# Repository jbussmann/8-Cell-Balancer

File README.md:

# 8-Cell Balancer Charger
This is the repository of a prototype 8-Cell Balancer Charger I have been working on for quite some time. If you would like to follow the development progress, feel free to visit my streams at https://www.twitch.tv/jbussmann where I usually work on this project.

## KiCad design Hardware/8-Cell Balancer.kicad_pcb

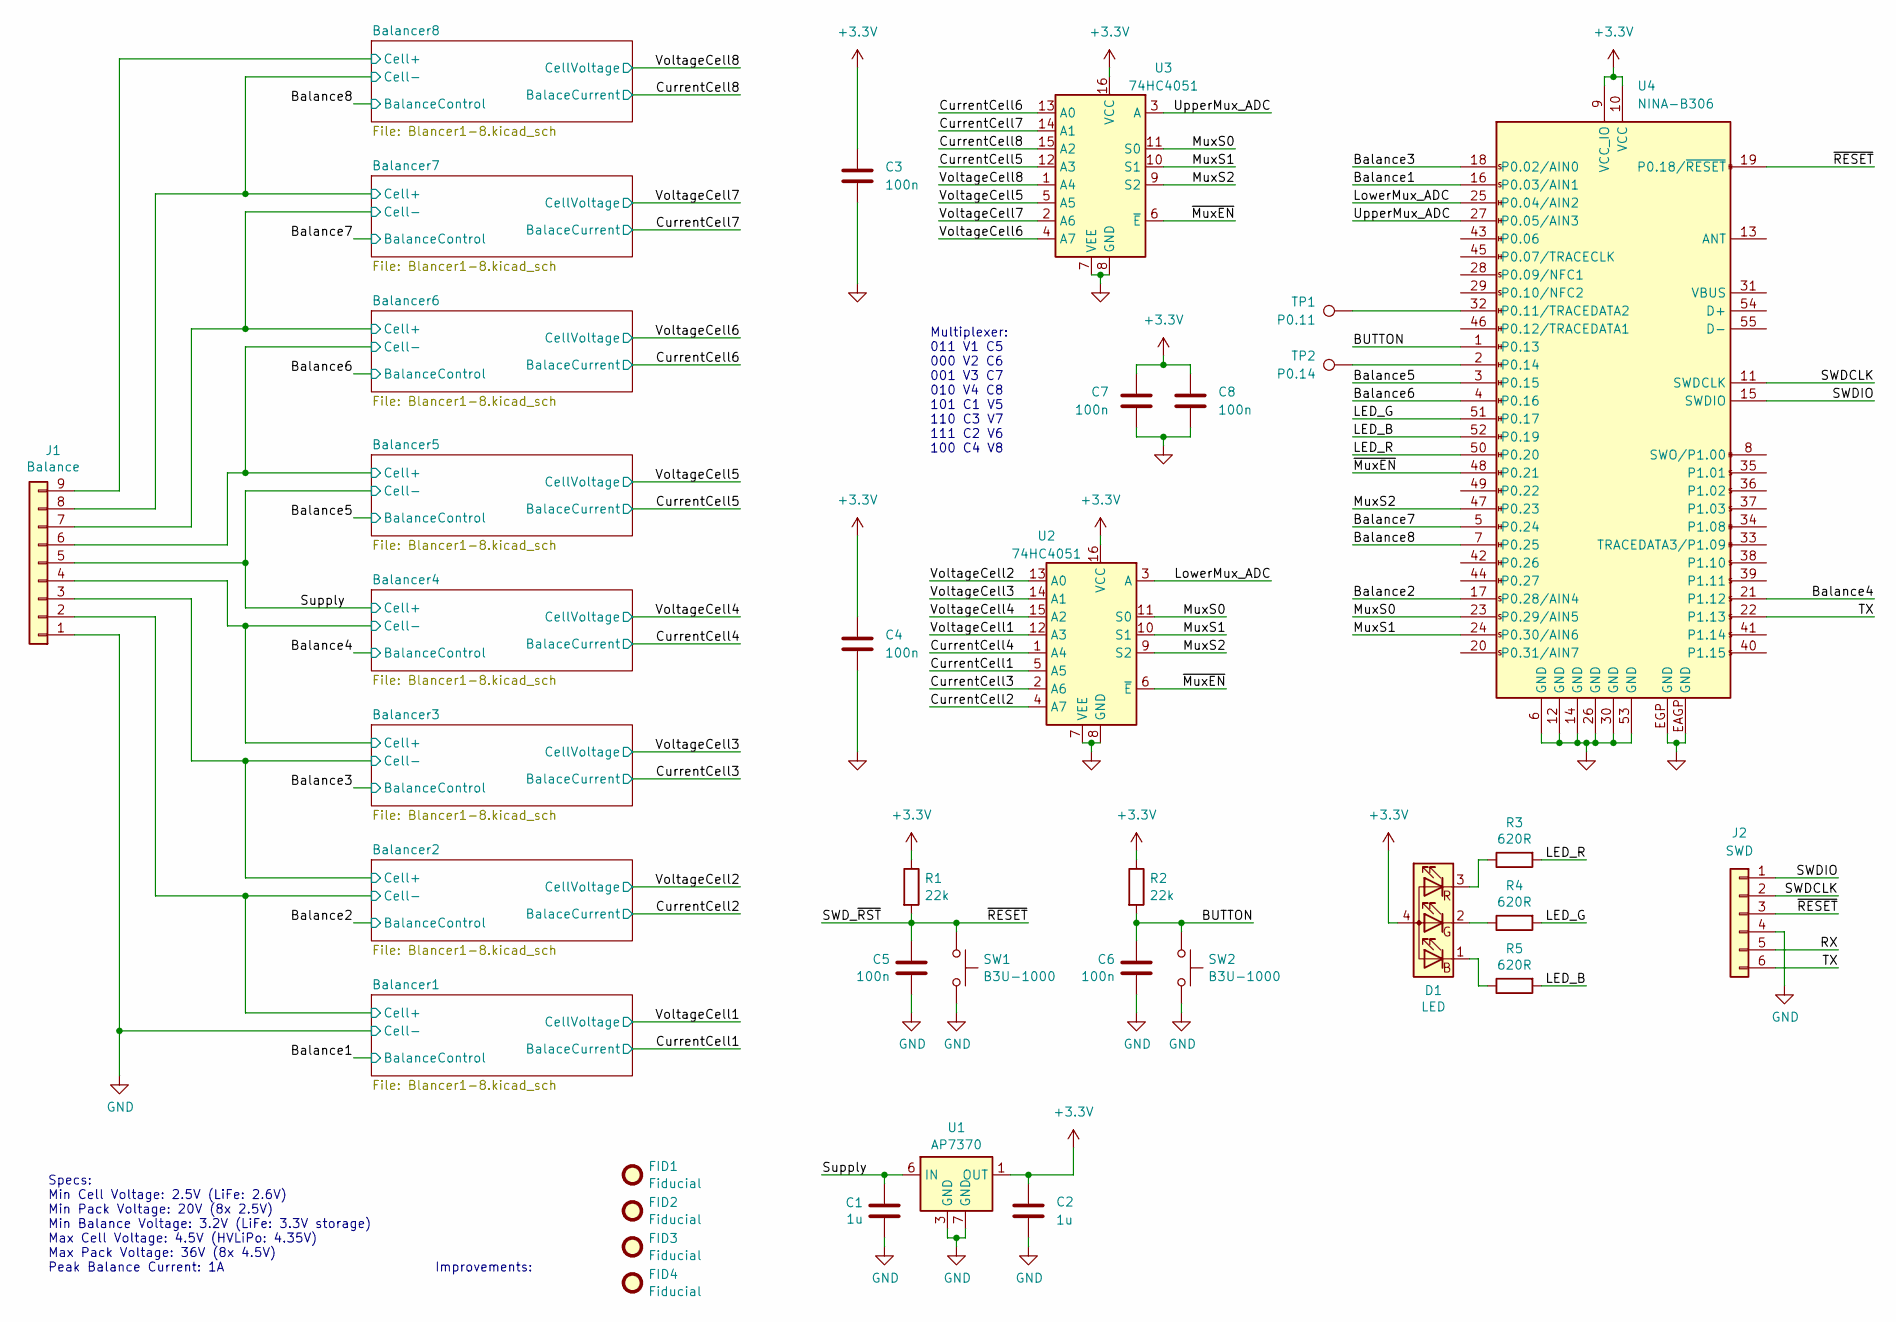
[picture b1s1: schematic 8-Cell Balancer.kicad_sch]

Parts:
C1, C2: 1u; C_0603_1608Metric; Mfr. Part# GRT188R61H105KE13D; Mouser Part# 81-GRT188R61H105KE3D
C3, C4, C5, C6, C7, C8: 100n; C_0402_1005Metric; Mfr. Part# GRM155R71C104KA88D; Mouser Part# 81-GRM155R71C104KA88
D1: LED; LED_RGB_1x1mm; Mfr. Part# UHD1110-FKA-CL1A13r3q1BBQFMF3; Mouser Part# 941-UHD0FKAC11BQFMF3
FID1, FID2, FID3, FID4: Fiducial; Fiducial_1mm_Mask2mm
J1: Balance; PinHeader_1x09_P2.54mm_Vertical
J2: SWD; PinHeader_1x06_P1.27mm_Vertical
R1, R2: 22k; R_0402_1005Metric; Mfr. Part# RC0402FR-0722KL; Mouser Part# 603-RC0402FR-0722KL
R3, R4, R5: 620R; R_0402_1005Metric; Mfr. Part# RC0402FR-07620RL; Mouser Part# 603-RC0402FR-07620RL
SW1, SW2: B3U-1000; Button_B3U-1000; Mfr. Part# B3U-1000P-B; Mouser Part# 653-B3U-1000P-B
TP1: P0.11; TestPoint_Pad_D1.0mm
TP2: P0.14; TestPoint_Pad_D1.0mm
U1: AP7370; Diodes_UDFN2020-6; Mfr. Part# AP7370-33FDC-7; Mouser Part# 621-AP7370-33FDC-7
U2, U3: 74HC4051; QFN-16-1EP_2.5x3.5mm_P0.5mm_EP1x2.5mm; Mfr. Part# 74LV4051BQ,115; Mouser Part# 771-LV4051BQ115
U4: NINA-B306; Module_ublox_NINA-B306; Mfr. Part# NINA-B306-00B; Mouser Part# 377-NINA-B306-00B

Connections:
+3.3V: C2.1, C3.1, C4.1, C7.1, C8.1, D1.4 (A), R1.1, R2.1, U1.1 (OUT), U2.16 (VCC), U3.16 (VCC), U4.9 (VCC_IO), U4.10 (VCC)
/BUTTON: C6.1, R2.2, SW2.1, U4.1 (P0.13)
/Balance1: U4.16 (P0.03/AIN1); also elsewhere on the board
/Balance2: U4.17 (P0.28/AIN4); also elsewhere on the board
/Balance3: U4.18 (P0.02/AIN0); also elsewhere on the board
/Balance4: U4.21 (P1.12); also elsewhere on the board
/Balance5: U4.3 (P0.15); also elsewhere on the board
/Balance6: U4.4 (P0.16); also elsewhere on the board
/Balance7: U4.5 (P0.24); also elsewhere on the board
/Balance8: U4.7 (P0.25); also elsewhere on the board
/Balancer1/Cell+: J1.2; also elsewhere on the board
/Balancer2/Cell+: J1.3; also elsewhere on the board
/Balancer3/Cell+: J1.4; also elsewhere on the board
/Balancer5/Cell+: J1.6; also elsewhere on the board
/Balancer6/Cell+: J1.7; also elsewhere on the board
/Balancer7/Cell+: J1.8; also elsewhere on the board
/Balancer8/Cell+: J1.9; also elsewhere on the board
/CurrentCell1: U2.5 (A5); also elsewhere on the board
/CurrentCell2: U2.4 (A7); also elsewhere on the board
/CurrentCell3: U2.2 (A6); also elsewhere on the board
/CurrentCell4: U2.1 (A4); also elsewhere on the board
/CurrentCell5: U3.12 (A3); also elsewhere on the board
/CurrentCell6: U3.13 (A0); also elsewhere on the board
/CurrentCell7: U3.14 (A1); also elsewhere on the board
/CurrentCell8: U3.15 (A2); also elsewhere on the board
/LED_B: R5.2, U4.52 (P0.19)
/LED_G: R4.2, U4.51 (P0.17)
/LED_R: R3.2, U4.50 (P0.20)
/LowerMux_ADC: U2.3 (A), U4.25 (P0.04/AIN2)
/MuxS0: U2.11 (S0), U3.11 (S0), U4.23 (P0.29/AIN5)
/MuxS1: U2.10 (S1), U3.10 (S1), U4.24 (P0.30/AIN6)
/MuxS2: U2.9 (S2), U3.9 (S2), U4.47 (P0.23)
/RX: J2.5
/SWDCLK: J2.2, U4.11 (SWDCLK)
/SWDIO: J2.1, U4.15 (SWDIO)
/SWD_~RST: C5.1, J2.3, R1.2, SW1.1, U4.19 (P0.18/~RESET)
/Supply: C1.1, J1.5, U1.6 (IN); also elsewhere on the board
/TX: J2.6, U4.22 (P1.13)
/UpperMux_ADC: U3.3 (A), U4.27 (P0.05/AIN3)
/VoltageCell1: U2.12 (A3); also elsewhere on the board
/VoltageCell2: U2.13 (A0); also elsewhere on the board
/VoltageCell3: U2.14 (A1); also elsewhere on the board
/VoltageCell4: U2.15 (A2); also elsewhere on the board
/VoltageCell5: U3.5 (A5); also elsewhere on the board
/VoltageCell6: U3.4 (A7); also elsewhere on the board
/VoltageCell7: U3.2 (A6); also elsewhere on the board
/VoltageCell8: U3.1 (A4); also elsewhere on the board
/~MuxEN: U2.6 (~E), U3.6 (~E), U4.48 (P0.21)
GND: C1.2, C2.2, C3.2, C4.2, C5.2, C6.2, C7.2, C8.2, J1.1, J2.4, SW1.2, SW2.2, U1.3 (GND), U1.7 (GND), U2.7 (VEE), U2.8 (GND), U3.7 (VEE), U3.8 (GND), U4.6 (GND), U4.12 (GND), U4.14 (GND), U4.26 (GND), U4.30 (GND), U4.53 (GND), U4.EAGP (GND), U4.EGP (GND); also elsewhere on the board
unnamed: D1.1 (BK), R5.1
unnamed: D1.2 (GK), R4.1
unnamed: D1.3 (RK), R3.1
unnamed: TP1.1, U4.32 (P0.11/TRACEDATA2)
unnamed: TP2.1, U4.2 (P0.14)

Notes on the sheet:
Improvements:
Specs: Min Cell Voltage: 2.5V (LiFe: 2.6V) Min Pack Voltage: 20V (8x 2.5V) Min Balance Voltage: 3.2V (LiFe: 3.3V storage) Max Cell Voltage: 4.5V (HVLiPo: 4.35V) Max Pack Voltage: 36V (8x 4.5V) Peak Balance Current: 1A
Multiplexer: 011 V1 C5 000 V2 C6 001 V3 C7 010 V4 C8 101 C1 V5 110 C3 V7 111 C2 V6 100 C4 V8

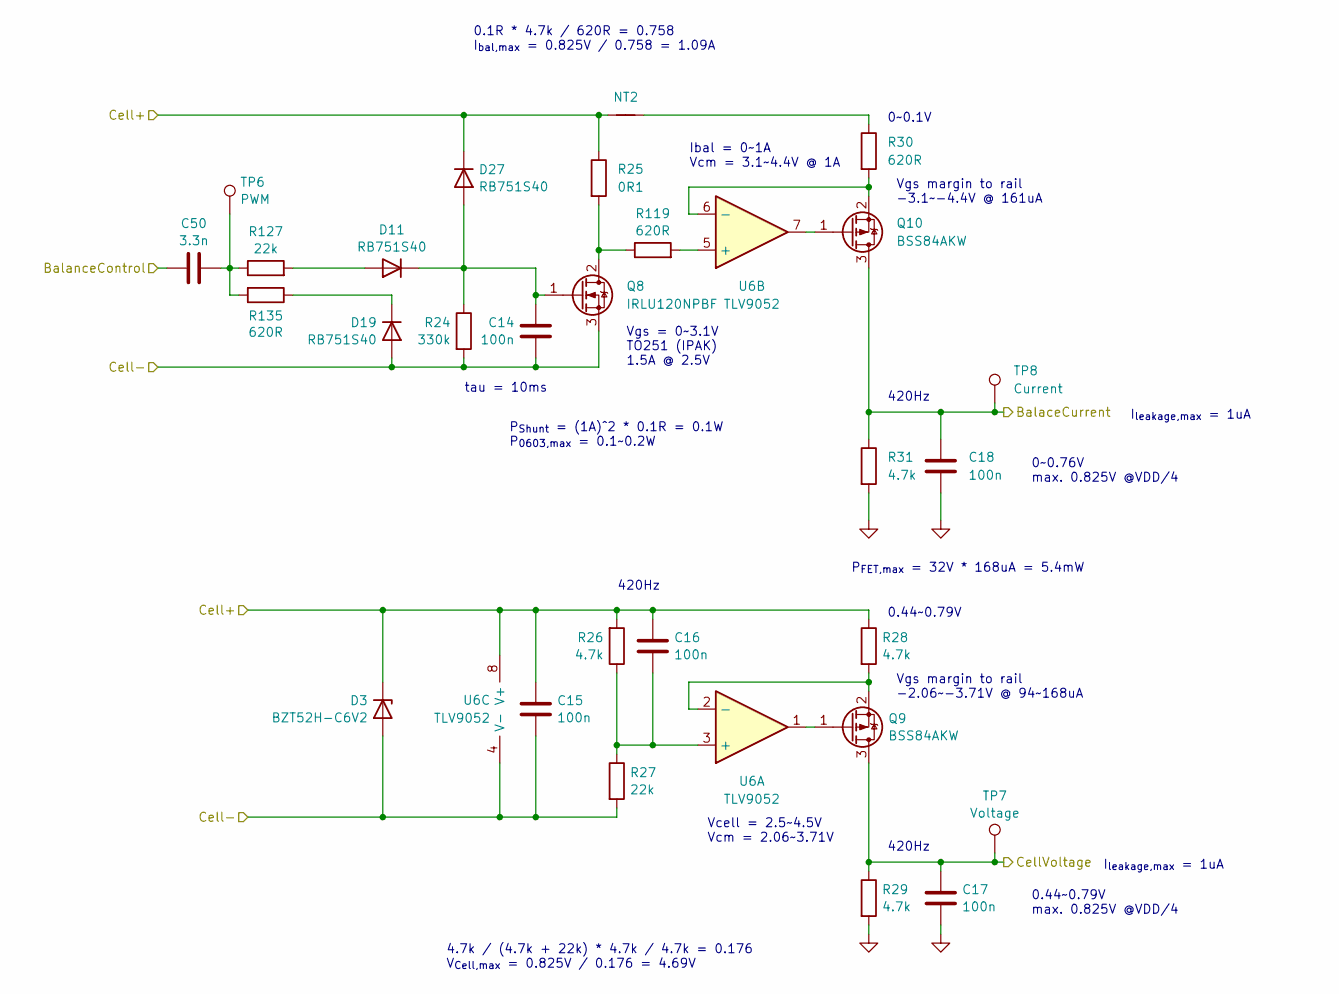
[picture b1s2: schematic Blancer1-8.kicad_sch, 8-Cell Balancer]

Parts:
C14, C15, C16, C17, C18: 100n; C_0402_1005Metric; Mfr. Part# GRM155R71C104KA88D; Mouser Part# 81-GRM155R71C104KA88
C50: 3.3n; C_0402_1005Metric; Mfr. Part# GRM1555C1H332JE01D; Mouser Part# 81-GRM1555C1H332JE1D
D3: BZT52H-C6V2; D_SOD-123F; Mfr. Part# BZT52H-C6V2,115; Mouser Part# 771-BZT52H-C6V2-T/R
D11, D19, D27: RB751S40; D_SOD-523; Mfr. Part# RB751S40T5G; Mouser Part# 863-RB751S40T5G
NT2: NetTie; NetTie-2_SMD_Pad0.127mm
Q8: IRLU120NPBF; TO-251-3_Flipped; Mfr. Part# IRLU120NPBF; Mouser Part# 942-IRLU120NPBF
Q9, Q10: BSS84AKW; SOT-323_SC-70; Mfr. Part# BSS84AKW,115; Mouser Part# 771-BSS84AKW115
R24: 330k; R_0402_1005Metric; Mfr. Part# RC0402FR-0722KL; Mouser Part# 603-RC0402FR-0722KL
R25: 0R1; R_0603_1608Metric; Mfr. Part# PT0603FR-7W0R1L; Mouser Part# 603-PT0603FR-7W0R1L
R26, R28, R29, R31: 4.7k; R_0402_1005Metric; Mfr. Part# RC0402FR-134K7L; Mouser Part# 603-RC0402FR-134K7L
R27, R127: 22k; R_0402_1005Metric; Mfr. Part# RC0402FR-0722KL; Mouser Part# 603-RC0402FR-0722KL
R30, R119, R135: 620R; R_0402_1005Metric; Mfr. Part# RC0402FR-07620RL; Mouser Part# 603-RC0402FR-07620RL
TP6: PWM; TestPoint_Pad_D1.0mm
TP7: Voltage; TestPoint_Pad_D1.0mm
TP8: Current; TestPoint_Pad_D1.0mm
U6: TLV9052; SOT-23-8; Mfr. Part# TLV9052IDDFR; Mouser Part# 595-TLV9052IDDFR

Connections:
/Balance2: C50.1; also elsewhere on the board
/Balancer1/Cell+: C14.2, C15.2, D3.2 (A), D19.2 (A), Q8.3 (S), R24.2, R27.2, U6.4 (V-); also elsewhere on the board
/Balancer2/Cell+: C15.1, C16.1, D3.1 (K), D27.1 (K), NT2.1, R25.1, R26.2, R28.1, U6.8 (V+); also elsewhere on the board
/CurrentCell2: C18.1, Q10.3 (D), R31.1, TP8.1; also elsewhere on the board
/VoltageCell2: C17.1, Q9.3 (D), R29.1, TP7.1; also elsewhere on the board
GND: C17.2, C18.2, R29.2, R31.2; also elsewhere on the board
unnamed: C50.2, R127.1, R135.2, TP6.1
unnamed: D11.2 (A), R127.2
unnamed: C14.1, D11.1 (K), D27.2 (A), Q8.1 (G), R24.1
unnamed: D19.1 (K), R135.1
unnamed: NT2.2, R30.1
unnamed: Q8.2 (D), R25.2, R119.1
unnamed: Q9.1 (G), U6.1
unnamed: Q9.2 (S), R28.2, U6.2 (-)
unnamed: Q10.1 (G), U6.7
unnamed: Q10.2 (S), R30.2, U6.6 (-)
unnamed: C16.2, R26.1, R27.1, U6.3 (+)
unnamed: R119.2, U6.5 (+)

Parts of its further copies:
C9, C10, C11, C12, C13, C19, C20, C21, C22, C23, C24, C25, C26, C27, C28, C29, C30, C31, C32, C33, C34, C35, C36, C37, C38, C39, C40, C41, C42, C43, C44, C45, C46, C47, C48: 100n; C_0402_1005Metric; Mfr. Part# GRM155R71C104KA88D; Mouser Part# 81-GRM155R71C104KA88
C49, C51, C52, C53, C54, C55, C56: 3.3n; C_0402_1005Metric; Mfr. Part# GRM1555C1H332JE01D; Mouser Part# 81-GRM1555C1H332JE1D
D2, D4, D5, D6, D7, D8, D9: BZT52H-C6V2; D_SOD-123F; Mfr. Part# BZT52H-C6V2,115; Mouser Part# 771-BZT52H-C6V2-T/R
D10, D12, D13, D14, D15, D16, D17, D18, D20, D21, D22, D23, D24, D25, D26, D28, D29, D30, D31, D32, D33: RB751S40; D_SOD-523; Mfr. Part# RB751S40T5G; Mouser Part# 863-RB751S40T5G
NT1, NT3, NT4, NT5, NT6, NT7, NT8: NetTie; NetTie-2_SMD_Pad0.127mm
Q3, Q13, Q18, Q23, Q28, Q33, Q38: IRLU120NPBF; TO-251-3_Flipped; Mfr. Part# IRLU120NPBF; Mouser Part# 942-IRLU120NPBF
Q4, Q5, Q14, Q15, Q19, Q20, Q24, Q25, Q29, Q30, Q34, Q35, Q39, Q40: BSS84AKW; SOT-323_SC-70; Mfr. Part# BSS84AKW,115; Mouser Part# 771-BSS84AKW115
R11, R37, R50, R63, R76, R89, R102: 330k; R_0402_1005Metric; Mfr. Part# RC0402FR-0722KL; Mouser Part# 603-RC0402FR-0722KL
R12, R38, R51, R64, R77, R90, R103: 0R1; R_0603_1608Metric; Mfr. Part# PT0603FR-7W0R1L; Mouser Part# 603-PT0603FR-7W0R1L
R13, R15, R16, R18, R39, R41, R42, R44, R52, R54, R55, R57, R65, R67, R68, R70, R78, R80, R81, R83, R91, R93, R94, R96, R104, R106, R107, R109: 4.7k; R_0402_1005Metric; Mfr. Part# RC0402FR-134K7L; Mouser Part# 603-RC0402FR-134K7L
R14, R40, R53, R66, R79, R92, R105, R126, R128, R129, R130, R131, R132, R133: 22k; R_0402_1005Metric; Mfr. Part# RC0402FR-0722KL; Mouser Part# 603-RC0402FR-0722KL
R17, R43, R56, R69, R82, R95, R108, R118, R120, R121, R122, R123, R124, R125, R134, R136, R137, R138, R139, R140, R141: 620R; R_0402_1005Metric; Mfr. Part# RC0402FR-07620RL; Mouser Part# 603-RC0402FR-07620RL
TP3, TP9, TP12, TP15, TP18, TP21, TP24: PWM; TestPoint_Pad_D1.0mm
TP4, TP10, TP13, TP16, TP19, TP22, TP25: Voltage; TestPoint_Pad_D1.0mm
TP5, TP11, TP14, TP17, TP20, TP23, TP26: Current; TestPoint_Pad_D1.0mm
U5, U7, U8, U9, U10, U11, U12: TLV9052; SOT-23-8; Mfr. Part# TLV9052IDDFR; Mouser Part# 595-TLV9052IDDFR

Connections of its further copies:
/Balance1: C49.1; also elsewhere on the board
/Balance3: C51.1; also elsewhere on the board
/Balance4: C52.1; also elsewhere on the board
/Balance5: C53.1; also elsewhere on the board
/Balance6: C54.1; also elsewhere on the board
/Balance7: C55.1; also elsewhere on the board
/Balance8: C56.1; also elsewhere on the board
/Balancer1/Cell+: C10.1, C11.1, D2.1 (K), D26.1 (K), NT1.1, R12.1, R13.2, R15.1, U5.8 (V+); also elsewhere on the board
/Balancer2/Cell+: C19.2, C20.2, D4.2 (A), D20.2 (A), Q13.3 (S), R37.2, R40.2, U7.4 (V-); also elsewhere on the board
/Balancer3/Cell+: C20.1, C21.1, C24.2, C25.2, D4.1 (K), D5.2 (A), D21.2 (A), D28.1 (K), NT3.1, Q18.3 (S), R38.1, R39.2, R41.1, R50.2, R53.2, U7.8 (V+), U8.4 (V-); also elsewhere on the board
/Balancer5/Cell+: C30.1, C31.1, C34.2, C35.2, D6.1 (K), D7.2 (A), D23.2 (A), D30.1 (K), NT5.1, Q28.3 (S), R64.1, R65.2, R67.1, R76.2, R79.2, U9.8 (V+), U10.4 (V-); also elsewhere on the board
/Balancer6/Cell+: C35.1, C36.1, C39.2, C40.2, D7.1 (K), D8.2 (A), D24.2 (A), D31.1 (K), NT6.1, Q33.3 (S), R77.1, R78.2, R80.1, R89.2, R92.2, U10.8 (V+), U11.4 (V-); also elsewhere on the board
/Balancer7/Cell+: C40.1, C41.1, C44.2, C45.2, D8.1 (K), D9.2 (A), D25.2 (A), D32.1 (K), NT7.1, Q38.3 (S), R90.1, R91.2, R93.1, R102.2, R105.2, U11.8 (V+), U12.4 (V-); also elsewhere on the board
/Balancer8/Cell+: C45.1, C46.1, D9.1 (K), D33.1 (K), NT8.1, R103.1, R104.2, R106.1, U12.8 (V+); also elsewhere on the board
/CurrentCell1: C13.1, Q5.3 (D), R18.1, TP5.1; also elsewhere on the board
/CurrentCell3: C23.1, Q15.3 (D), R44.1, TP11.1; also elsewhere on the board
/CurrentCell4: C28.1, Q20.3 (D), R57.1, TP14.1; also elsewhere on the board
/CurrentCell5: C33.1, Q25.3 (D), R70.1, TP17.1; also elsewhere on the board
/CurrentCell6: C38.1, Q30.3 (D), R83.1, TP20.1; also elsewhere on the board
/CurrentCell7: C43.1, Q35.3 (D), R96.1, TP23.1; also elsewhere on the board
/CurrentCell8: C48.1, Q40.3 (D), R109.1, TP26.1; also elsewhere on the board
/Supply: C25.1, C26.1, C29.2, C30.2, D5.1 (K), D6.2 (A), D22.2 (A), D29.1 (K), NT4.1, Q23.3 (S), R51.1, R52.2, R54.1, R63.2, R66.2, U8.8 (V+), U9.4 (V-); also elsewhere on the board
/VoltageCell1: C12.1, Q4.3 (D), R16.1, TP4.1; also elsewhere on the board
/VoltageCell3: C22.1, Q14.3 (D), R42.1, TP10.1; also elsewhere on the board
/VoltageCell4: C27.1, Q19.3 (D), R55.1, TP13.1; also elsewhere on the board
/VoltageCell5: C32.1, Q24.3 (D), R68.1, TP16.1; also elsewhere on the board
/VoltageCell6: C37.1, Q29.3 (D), R81.1, TP19.1; also elsewhere on the board
/VoltageCell7: C42.1, Q34.3 (D), R94.1, TP22.1; also elsewhere on the board
/VoltageCell8: C47.1, Q39.3 (D), R107.1, TP25.1; also elsewhere on the board
GND: C9.2, C10.2, C12.2, C13.2, C22.2, C23.2, C27.2, C28.2, C32.2, C33.2, C37.2, C38.2, C42.2, C43.2, C47.2, C48.2, D2.2 (A), D18.2 (A), Q3.3 (S), R11.2, R14.2, R16.2, R18.2, R42.2, R44.2, R55.2, R57.2, R68.2, R70.2, R81.2, R83.2, R94.2, R96.2, R107.2, R109.2, U5.4 (V-); also elsewhere on the board
unnamed: C49.2, R126.1, R134.2, TP3.1
unnamed: C51.2, R128.1, R136.2, TP9.1
unnamed: C52.2, R129.1, R137.2, TP12.1
unnamed: C53.2, R130.1, R138.2, TP15.1
unnamed: C54.2, R131.1, R139.2, TP18.1
unnamed: C55.2, R132.1, R140.2, TP21.1
unnamed: C56.2, R133.1, R141.2, TP24.1
unnamed: D10.2 (A), R126.2
unnamed: C9.1, D10.1 (K), D26.2 (A), Q3.1 (G), R11.1
unnamed: D12.2 (A), R128.2
unnamed: C19.1, D12.1 (K), D28.2 (A), Q13.1 (G), R37.1
unnamed: D13.2 (A), R129.2
unnamed: C24.1, D13.1 (K), D29.2 (A), Q18.1 (G), R50.1
unnamed: D14.2 (A), R130.2
unnamed: C29.1, D14.1 (K), D30.2 (A), Q23.1 (G), R63.1
unnamed: D15.2 (A), R131.2
unnamed: C34.1, D15.1 (K), D31.2 (A), Q28.1 (G), R76.1
unnamed: D16.2 (A), R132.2
unnamed: C39.1, D16.1 (K), D32.2 (A), Q33.1 (G), R89.1
unnamed: D17.2 (A), R133.2
unnamed: C44.1, D17.1 (K), D33.2 (A), Q38.1 (G), R102.1
unnamed: D18.1 (K), R134.1
unnamed: D20.1 (K), R136.1
unnamed: D21.1 (K), R137.1
unnamed: D22.1 (K), R138.1
unnamed: D23.1 (K), R139.1
unnamed: D24.1 (K), R140.1
unnamed: D25.1 (K), R141.1
unnamed: NT1.2, R17.1
unnamed: NT3.2, R43.1
unnamed: NT4.2, R56.1
unnamed: NT5.2, R69.1
unnamed: NT6.2, R82.1
unnamed: NT7.2, R95.1
unnamed: NT8.2, R108.1
unnamed: Q3.2 (D), R12.2, R118.1
unnamed: Q4.1 (G), U5.1
unnamed: Q4.2 (S), R15.2, U5.2 (-)
unnamed: Q5.1 (G), U5.7
unnamed: Q5.2 (S), R17.2, U5.6 (-)
unnamed: Q13.2 (D), R38.2, R120.1
unnamed: Q14.1 (G), U7.1
unnamed: Q14.2 (S), R41.2, U7.2 (-)
unnamed: Q15.1 (G), U7.7
unnamed: Q15.2 (S), R43.2, U7.6 (-)
unnamed: Q18.2 (D), R51.2, R121.1
unnamed: Q19.1 (G), U8.1
unnamed: Q19.2 (S), R54.2, U8.2 (-)
unnamed: Q20.1 (G), U8.7
unnamed: Q20.2 (S), R56.2, U8.6 (-)
unnamed: Q23.2 (D), R64.2, R122.1
unnamed: Q24.1 (G), U9.1
unnamed: Q24.2 (S), R67.2, U9.2 (-)
unnamed: Q25.1 (G), U9.7
unnamed: Q25.2 (S), R69.2, U9.6 (-)
unnamed: Q28.2 (D), R77.2, R123.1
unnamed: Q29.1 (G), U10.1
unnamed: Q29.2 (S), R80.2, U10.2 (-)
unnamed: Q30.1 (G), U10.7
unnamed: Q30.2 (S), R82.2, U10.6 (-)
unnamed: Q33.2 (D), R90.2, R124.1
unnamed: Q34.1 (G), U11.1
unnamed: Q34.2 (S), R93.2, U11.2 (-)
unnamed: Q35.1 (G), U11.7
unnamed: Q35.2 (S), R95.2, U11.6 (-)
unnamed: Q38.2 (D), R103.2, R125.1
unnamed: Q39.1 (G), U12.1
unnamed: Q39.2 (S), R106.2, U12.2 (-)
unnamed: Q40.1 (G), U12.7
unnamed: Q40.2 (S), R108.2, U12.6 (-)
unnamed: C11.2, R13.1, R14.1, U5.3 (+)
unnamed: R118.2, U5.5 (+)
unnamed: C21.2, R39.1, R40.1, U7.3 (+)
unnamed: R120.2, U7.5 (+)
unnamed: C26.2, R52.1, R53.1, U8.3 (+)
unnamed: R121.2, U8.5 (+)
unnamed: C31.2, R65.1, R66.1, U9.3 (+)
unnamed: R122.2, U9.5 (+)
unnamed: C36.2, R78.1, R79.1, U10.3 (+)
unnamed: R123.2, U10.5 (+)
unnamed: C41.2, R91.1, R92.1, U11.3 (+)
unnamed: R124.2, U11.5 (+)
unnamed: C46.2, R104.1, R105.1, U12.3 (+)
unnamed: R125.2, U12.5 (+)

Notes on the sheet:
P_{FET,max} = 32V * 168uA = 5.4mW
420Hz
tau = 10ms
Vgs margin to rail -3.1~-4.4V @ 161uA
I_{leakage,max} = 1uA
P_{Shunt} = (1A)^2 * 0.1R = 0.1W P_{0603,max} = 0.1~0.2W
0.44~0.79V max. 0.825V @VDD/4
Vgs margin to rail -2.06~-3.71V @ 94~168uA
Vgs = 0~3.1V TO251 (IPAK) 1.5A @ 2.5V
Ibal = 0~1A Vcm = 3.1~4.4V @ 1A
4.7k / (4.7k + 22k) * 4.7k / 4.7k = 0.176 V_{Cell,max} = 0.825V / 0.176 = 4.69V
0.44~0.79V
0.1R * 4.7k / 620R = 0.758 I_{bal,max} = 0.825V / 0.758 = 1.09A
0~0.76V max. 0.825V @VDD/4
0~0.1V
Vcell = 2.5~4.5V Vcm = 2.06~3.71V

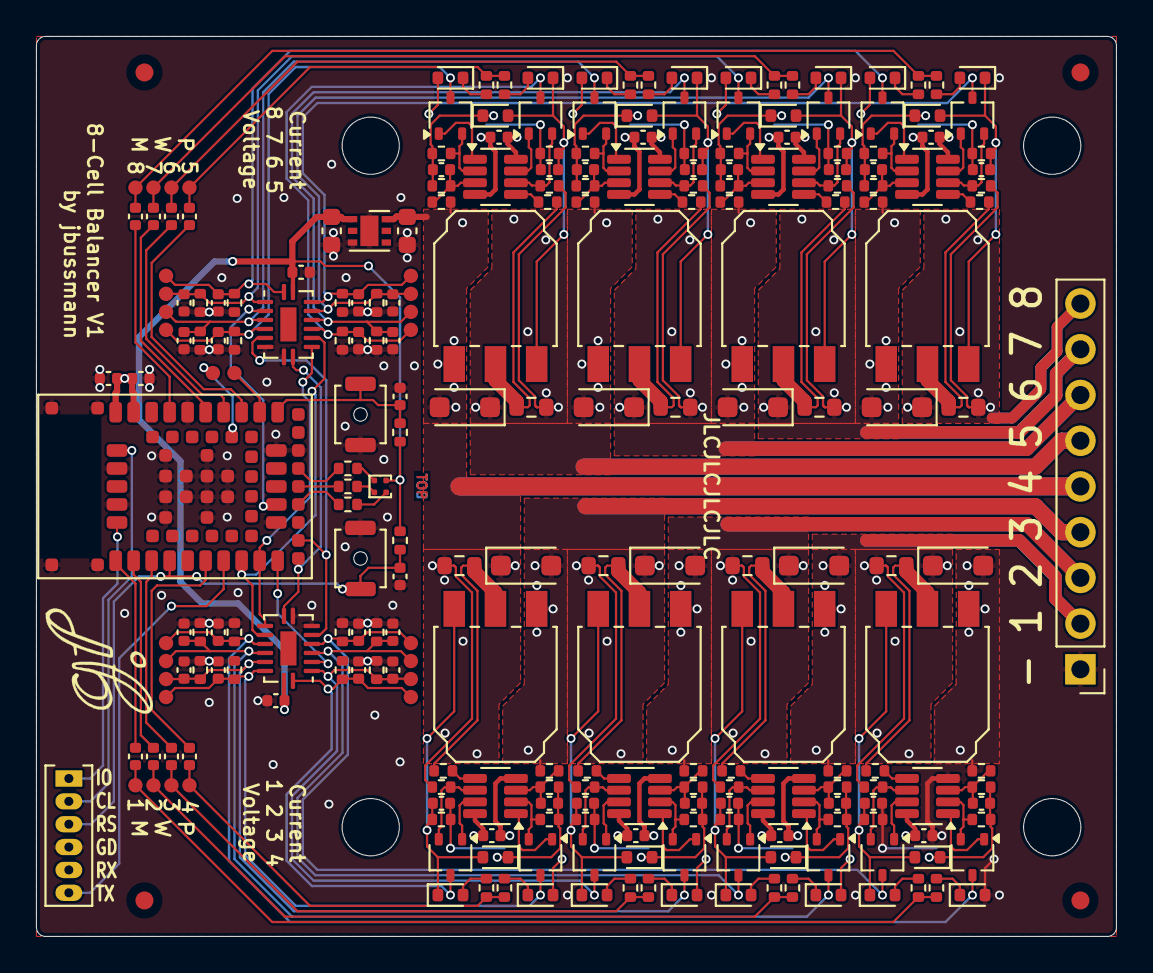
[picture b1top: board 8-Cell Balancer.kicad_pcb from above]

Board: 2 copper layers, 60.0 x 50.0 mm, 260 parts (0 on the bottom side), 149 nets.

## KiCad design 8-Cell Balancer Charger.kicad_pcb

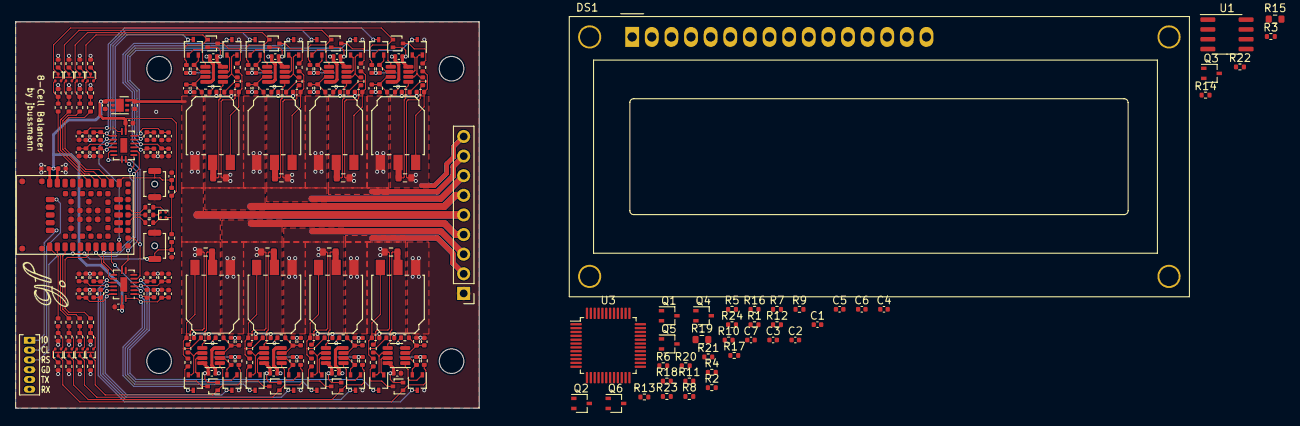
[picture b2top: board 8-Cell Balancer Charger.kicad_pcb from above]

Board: 2 copper layers, 60.0 x 50.0 mm, 262 parts (0 on the bottom side), 169 nets.

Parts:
C1, C4, C5, C6, C7: C; C_0402_1005Metric
C2, C3: CP; C_0402_1005Metric
C8, C9, C10, C11, C13, C14, C15, C16, C17, C18, C19, C20, C21, C22, C23, C24, C25, C26, C27, C28, C29, C30, C31, C32, C33, C34, C35, C36, C37, C38, C41, C42, C43, C44, C45, C46, C47, C48, C49, C50, C51, C52, C53, C54, C55, C56: 100n; C_0402_1005Metric
C39, C40: 1u; C_0402_1005Metric
D3: LED; LED_RGB_1x1mm
DS1: WC1602A
J4: Balance; PinHeader_1x09_P2.54mm_Vertical
J5: Conn_01x06; PinHeader_1x06_P1.27mm_Vertical
NT1, NT2, NT3, NT4, NT5, NT6, NT7, NT8: NetTie_2; NetTie-2_SMD_Pad0.127mm
Q1, Q3, Q4, Q5, Q6: Q_NMOS_DGS; SOT-323_SC-70
Q2: Q_PMOS_DGS; SOT-323_SC-70
Q7, Q12, Q17, Q22, Q27, Q32, Q37, Q42: PMXB360ENEA; DFN1010-3
Q8, Q13, Q18, Q23, Q28, Q33, Q38, Q43: 2SA1832; SOT-416
Q9, Q14, Q19, Q24, Q29, Q34, Q39, Q44: IRLU120NPBF; TO-251-3_Flipped
Q10, Q11, Q15, Q16, Q20, Q21, Q25, Q26, Q30, Q31, Q35, Q36, Q40, Q41, Q45, Q46: BSS84AKW; SOT-323_SC-70
R1, R2, R3, R4, R6, R7, R8, R10, R11, R12, R13, R14, R17, R20, R21, R22, R23, R24: R; R_0402_1005Metric
R5, R9, R16, R18, R31, R35, R37, R39, R44, R48, R50, R52, R57, R61, R63, R65, R70, R74, R76, R78, R83, R87, R89, R91, R96, R100, R102, R104, R109, R113, R115, R117, R122, R126, R128, R130: 100k; R_0402_1005Metric
R15, R19: 0R5; R_0603_1608Metric
R25, R26: 51k; R_0402_1005Metric
R27, R28, R29: 1.8k; R_0402_1005Metric
R30, R43, R56, R69, R82, R95, R108, R121: 1k; R_0402_1005Metric
R32, R33, R34, R41, R45, R46, R47, R54, R58, R59, R60, R67, R71, R72, R73, R80, R84, R85, R86, R93, R97, R98, R99, R106, R110, R111, R112, R119, R123, R124, R125, R132: 10k; R_0402_1005Metric
R36, R49, R62, R75, R88, R101, R114, R127: 0R1; R_0603_1608Metric
R38, R40, R51, R53, R64, R66, R77, R79, R90, R92, R103, R105, R116, R118, R129, R131: 270k; R_0402_1005Metric
R42, R55, R68, R81, R94, R107, R120, R133: 330k; R_0402_1005Metric
SW5: Reset; Button_B3U-1000
SW6: Button; Button_B3U-1000
U1: FAN3278; SOIC-8_3.9x4.9mm_P1.27mm
U3: ATmega4809-A; TQFP-48_7x7mm_P0.5mm
U6, U7: 74HC4051; QFN-16-1EP_2.5x3.5mm_P0.5mm_EP1x2.5mm
U8: Module_NINA-B306; Module_ublox_NINA-B306
U9, U10, U11, U12, U13, U14, U15, U16: TLV9052; SOT-23-8
U17: LDO_Diodes_AP7370; Diodes_UDFN2020-6

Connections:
5V: C7.1, DS1.2 (VDD), DS1.15 (LED(+)), R3.1, U3.14 (VCC), U3.28 (AVCC), U3.42 (VCC)
+3.3V: C8.1, C9.1, C13.1, C14.1, C40.1, D3.4 (A), R25.1, R26.1, U6.16 (VCC), U7.16 (VCC), U8.9 (VCC_IO), U8.10 (VCC), U17.1 (OUT)
/Balancer/BUTTON: C11.1, R26.2, SW6.1, U8.1 (P0.13)
/Balancer/Balance1: R121.2, U8.16 (P0.03/AIN1)
/Balancer/Balance2: R108.2, U8.17 (P0.28/AIN4)
/Balancer/Balance3: R95.2, U8.18 (P0.02/AIN0)
/Balancer/Balance4: R82.2, U8.21 (P1.12)
/Balancer/Balance5: R69.2, U8.2 (P0.14)
/Balancer/Balance6: R56.2, U8.3 (P0.15)
/Balancer/Balance7: R43.2, U8.4 (P0.16)
/Balancer/Balance8: R30.2, U8.5 (P0.24)
/Balancer/BalanceCurrent: U6.3 (A), U8.24 (P0.30/AIN6)
/Balancer/Balancer1/Cell+: C33.2, C34.2, C35.2, C37.1, J4.2, NT8.1, Q39.3 (S), Q43.2 (E), R113.2, R116.2, R124.1, R127.1, R128.2, R130.1, U15.4 (V-), U16.8 (V+)
/Balancer/Balancer2/Cell+: C30.2, C31.2, C32.2, C34.1, J4.3, NT7.1, Q34.3 (S), Q38.2 (E), R100.2, R103.2, R111.1, R114.1, R115.2, R117.1, U14.4 (V-), U15.8 (V+)
/Balancer/Balancer3/Cell+: C27.2, C28.2, C29.2, C31.1, J4.4, NT6.1, Q29.3 (S), Q33.2 (E), R87.2, R90.2, R98.1, R101.1, R102.2, R104.1, U13.4 (V-), U14.8 (V+)
/Balancer/Balancer5/Cell+: C21.2, C22.2, C23.2, C25.1, J4.6, NT4.1, Q19.3 (S), Q23.2 (E), R61.2, R64.2, R72.1, R75.1, R76.2, R78.1, U11.4 (V-), U12.8 (V+)
/Balancer/Balancer6/Cell+: C18.2, C19.2, C20.2, C22.1, J4.7, NT3.1, Q14.3 (S), Q18.2 (E), R48.2, R51.2, R59.1, R62.1, R63.2, R65.1, U10.4 (V-), U11.8 (V+)
/Balancer/Balancer7/Cell+: C15.2, C16.2, C17.2, C19.1, J4.8, NT2.1, Q9.3 (S), Q13.2 (E), R35.2, R38.2, R46.1, R49.1, R50.2, R52.1, U9.4 (V-), U10.8 (V+)
/Balancer/Balancer8/Cell+: C16.1, J4.9, NT1.1, Q8.2 (E), R33.1, R36.1, R37.2, R39.1, U9.8 (V+)
/Balancer/CellVoltage: U7.3 (A), U8.25 (P0.04/AIN2)
/Balancer/CurrentCell1: C56.1, Q46.3 (D), R133.1, U6.5 (A5)
/Balancer/CurrentCell2: C54.1, Q41.3 (D), R120.1, U6.4 (A7)
/Balancer/CurrentCell3: C52.1, Q36.3 (D), R107.1, U6.2 (A6)
/Balancer/CurrentCell4: C50.1, Q31.3 (D), R94.1, U6.1 (A4)
/Balancer/CurrentCell5: C48.1, Q26.3 (D), R81.1, U7.12 (A3)
/Balancer/CurrentCell6: C46.1, Q21.3 (D), R68.1, U7.13 (A0)
/Balancer/CurrentCell7: C44.1, Q16.3 (D), R55.1, U7.14 (A1)
/Balancer/CurrentCell8: C42.1, Q11.3 (D), R42.1, U7.15 (A2)
/Balancer/LED_B: R29.2, U8.52 (P0.19)
/Balancer/LED_G: R28.2, U8.51 (P0.17)
/Balancer/LED_R: R27.2, U8.50 (P0.20)
/Balancer/MuxS0: U6.11 (S0), U7.11 (S0), U8.22 (P1.13)
/Balancer/MuxS1: U6.10 (S1), U7.10 (S1), U8.23 (P0.29/AIN5)
/Balancer/MuxS2: U6.9 (S2), U7.9 (S2), U8.47 (P0.23)
/Balancer/SWDCLK: J5.2, U8.11 (SWDCLK)
/Balancer/SWDIO: J5.1, U8.15 (SWDIO)
/Balancer/SWD_~RST: C10.1, J5.3, R25.2, SW5.1, U8.19 (P0.18/~RESET)
/Balancer/Supply: C24.2, C25.2, C26.2, C28.1, C39.1, J4.5, NT5.1, Q24.3 (S), Q28.2 (E), R74.2, R77.2, R85.1, R88.1, R89.2, R91.1, U12.4 (V-), U13.8 (V+), U17.6 (IN)
/Balancer/VoltageCell1: C55.1, Q45.3 (D), R131.1, U6.12 (A3)
/Balancer/VoltageCell2: C53.1, Q40.3 (D), R118.1, U6.13 (A0)
/Balancer/VoltageCell3: C51.1, Q35.3 (D), R105.1, U6.14 (A1)
/Balancer/VoltageCell4: C49.1, Q30.3 (D), R92.1, U6.15 (A2)
/Balancer/VoltageCell5: C47.1, Q25.3 (D), R79.1, U7.5 (A5)
/Balancer/VoltageCell6: C45.1, Q20.3 (D), R66.1, U7.4 (A7)
/Balancer/VoltageCell7: C43.1, Q15.3 (D), R53.1, U7.2 (A6)
/Balancer/VoltageCell8: C41.1, Q10.3 (D), R40.1, U7.1 (A4)
/Balancer/~MuxEN: U6.6 (~E), U7.6 (~E), U8.48 (P0.21)
/DischargeShunt: Q4.3 (S), R19.1
/FwOut: Q5.2 (G), R22.1
/OutputShunt: Q5.1 (D), R15.1, R17.2, R19.2
/RevOut: Q6.2 (G), R24.1
/Vout+: C3.1, Q4.1 (D)
BoostFET: Q3.2 (G), R12.1, U1.7 (OUTA)
BuckFET: Q2.2 (G), R6.2, U1.5 (~OUTB)
DischargeFet: Q4.2 (G), R17.1
GND: C2.2, C3.2, C4.2, C5.2, C6.2, C7.2, C8.2, C9.2, C10.2, C11.2, C13.2, C14.2, C36.2, C37.2, C38.2, C39.2, C40.2, C41.2, C42.2, C43.2, C44.2, C45.2, C46.2, C47.2, C48.2, C49.2, C50.2, C51.2, C52.2, C53.2, C54.2, C55.2, C56.2, DS1.1 (VSS), DS1.5 (R/W), DS1.7 (D0), DS1.8 (D1), DS1.9 (D2), DS1.10 (D3), DS1.16 (LED(-)), J4.1, J5.4, Q1.3 (S), Q3.3 (S), Q44.3 (S), R4.2, R5.2, R8.2, R11.2, R12.2, R14.2, R15.2, R16.2, R31.2, R32.2, R40.2, R42.2, R44.2, R45.2, R53.2, R55.2, R57.2, R58.2, R66.2, R68.2, R70.2, R71.2, R79.2, R81.2, R83.2, R84.2, R92.2, R94.2, R96.2, R97.2, R105.2, R107.2, R109.2, R110.2, R118.2, R120.2, R122.2, R123.2, R126.2, R129.2, R131.2, R133.2, SW5.2, SW6.2, U1.3 (GND), U3.15 (GND), U3.29 (GND), U3.43 (GND), U6.7 (VEE), U6.8 (GND), U7.7 (VEE), U7.8 (GND), U8.6 (GND), U8.12 (GND), U8.14 (GND), U8.26 (GND), U8.30 (GND), U8.53 (GND), U8.EAGP (GND), U8.EGP (GND), U16.4 (V-), U17.3 (GND), U17.7 (GND)
InputVoltage: R7.2, R8.1
unnamed: C1.1, Q1.2 (G), R1.2, R2.1
unnamed: C5.1, R21.1
unnamed: C15.1, Q9.1 (G), R34.2, R35.1
unnamed: C17.1, R37.1, R38.1, U9.3 (+)
unnamed: C18.1, Q14.1 (G), R47.2, R48.1
unnamed: C20.1, R50.1, R51.1, U10.3 (+)
unnamed: C21.1, Q19.1 (G), R60.2, R61.1
unnamed: C23.1, R63.1, R64.1, U11.3 (+)
unnamed: C24.1, Q24.1 (G), R73.2, R74.1
unnamed: C26.1, R76.1, R77.1, U12.3 (+)
unnamed: C27.1, Q29.1 (G), R86.2, R87.1
unnamed: C29.1, R89.1, R90.1, U13.3 (+)
unnamed: C30.1, Q34.1 (G), R99.2, R100.1
unnamed: C32.1, R102.1, R103.1, U14.3 (+)
unnamed: C33.1, Q39.1 (G), R112.2, R113.1
unnamed: C35.1, R115.1, R116.1, U15.3 (+)
unnamed: C36.1, Q44.1 (G), R125.2, R126.1
unnamed: C38.1, R128.1, R129.1, U16.3 (+)
unnamed: D3.1 (BK), R29.1
unnamed: D3.2 (GK), R28.1
unnamed: D3.3 (RK), R27.1
unnamed: NT1.2, R41.1
unnamed: NT2.2, R54.1
unnamed: NT3.2, R67.1
unnamed: NT4.2, R80.1
unnamed: NT5.2, R93.1
unnamed: NT6.2, R106.1
unnamed: NT7.2, R119.1
unnamed: NT8.2, R132.1
unnamed: Q5.3 (S), Q6.3 (S), R22.2, R24.2
unnamed: Q7.1 (G), R30.1, R31.1
unnamed: Q7.2 (S), R32.1
unnamed: Q7.3 (D), Q8.1 (B), R33.2
unnamed: Q8.3 (C), R34.1
unnamed: Q9.2 (D), R36.2, U9.5 (+)
unnamed: Q10.1 (G), U9.1
unnamed: Q10.2 (S), R39.2, U9.2 (-)
unnamed: Q11.1 (G), U9.7
unnamed: Q11.2 (S), R41.2, U9.6 (-)
unnamed: Q12.1 (G), R43.1, R44.1
unnamed: Q12.2 (S), R45.1
unnamed: Q12.3 (D), Q13.1 (B), R46.2
unnamed: Q13.3 (C), R47.1
unnamed: Q14.2 (D), R49.2, U10.5 (+)
unnamed: Q15.1 (G), U10.1
unnamed: Q15.2 (S), R52.2, U10.2 (-)
unnamed: Q16.1 (G), U10.7
unnamed: Q16.2 (S), R54.2, U10.6 (-)
unnamed: Q17.1 (G), R56.1, R57.1
unnamed: Q17.2 (S), R58.1
unnamed: Q17.3 (D), Q18.1 (B), R59.2
unnamed: Q18.3 (C), R60.1
unnamed: Q19.2 (D), R62.2, U11.5 (+)
unnamed: Q20.1 (G), U11.1
unnamed: Q20.2 (S), R65.2, U11.2 (-)
unnamed: Q21.1 (G), U11.7
unnamed: Q21.2 (S), R67.2, U11.6 (-)
unnamed: Q22.1 (G), R69.1, R70.1
unnamed: Q22.2 (S), R71.1
unnamed: Q22.3 (D), Q23.1 (B), R72.2
unnamed: Q23.3 (C), R73.1
unnamed: Q24.2 (D), R75.2, U12.5 (+)
unnamed: Q25.1 (G), U12.1
unnamed: Q25.2 (S), R78.2, U12.2 (-)
unnamed: Q26.1 (G), U12.7
unnamed: Q26.2 (S), R80.2, U12.6 (-)
unnamed: Q27.1 (G), R82.1, R83.1
unnamed: Q27.2 (S), R84.1
unnamed: Q27.3 (D), Q28.1 (B), R85.2
unnamed: Q28.3 (C), R86.1
unnamed: Q29.2 (D), R88.2, U13.5 (+)
unnamed: Q30.1 (G), U13.1
unnamed: Q30.2 (S), R91.2, U13.2 (-)
unnamed: Q31.1 (G), U13.7
unnamed: Q31.2 (S), R93.2, U13.6 (-)
unnamed: Q32.1 (G), R95.1, R96.1
unnamed: Q32.2 (S), R97.1
unnamed: Q32.3 (D), Q33.1 (B), R98.2
unnamed: Q33.3 (C), R99.1
unnamed: Q34.2 (D), R101.2, U14.5 (+)
unnamed: Q35.1 (G), U14.1
unnamed: Q35.2 (S), R104.2, U14.2 (-)
unnamed: Q36.1 (G), U14.7
unnamed: Q36.2 (S), R106.2, U14.6 (-)
unnamed: Q37.1 (G), R108.1, R109.1
unnamed: Q37.2 (S), R110.1
unnamed: Q37.3 (D), Q38.1 (B), R111.2
unnamed: Q38.3 (C), R112.1
unnamed: Q39.2 (D), R114.2, U15.5 (+)
unnamed: Q40.1 (G), U15.1
unnamed: Q40.2 (S), R117.2, U15.2 (-)
unnamed: Q41.1 (G), U15.7
unnamed: Q41.2 (S), R119.2, U15.6 (-)
unnamed: Q42.1 (G), R121.1, R122.1
unnamed: Q42.2 (S), R123.1
unnamed: Q42.3 (D), Q43.1 (B), R124.2
unnamed: Q43.3 (C), R125.1
unnamed: Q44.2 (D), R127.2, U16.5 (+)
unnamed: Q45.1 (G), U16.1
unnamed: Q45.2 (S), R130.2, U16.2 (-)
unnamed: Q46.1 (G), U16.7
unnamed: Q46.2 (S), R132.2, U16.6 (-)
unnamed: R5.1, R9.2
unnamed: R16.1, R18.2
unnamed: R18.1, R20.2
OutputCurrent: C4.1, R20.1
OutputVoltage: R10.2, R11.1
ReverseVoltage: R13.2, R14.1
SMPSEnable: U1.1 (ENA), U1.8 (ENB)
Temperature: R3.2, R4.1
VIn+: C2.1, C6.1, Q2.3 (S), R1.1, R6.1, R7.1, U1.6 (VDD)
VIn-: C1.2, Q1.1 (D), R2.2

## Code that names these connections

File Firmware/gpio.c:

#include "gpio.h"

#include "nrfx_gpiote.h"
#include "pwm.h"

#define NRF_LOG_MODULE_NAME gpio
#include "log.h"
NRF_LOG_MODULE_REGISTER();

static void gpiote_event_handler(nrfx_gpiote_pin_t pin,
                                 nrf_gpiote_polarity_t action) {
  switch (pin) {
    case BUTTON_PIN:
      if (nrf_gpio_pin_read(BUTTON_PIN)) {
        // NRF_LOG_DEBUG("Button released");
      } else {
        pwm_toggle_balancer_state();
        // NRF_LOG_DEBUG("Button pressed");
      }
      break;
    default:
      NRF_LOG_WARNING("undefined event on pin: %i", pin);
      break;
  }
}

static void gpio_init_led_pins(void) {
  const uint8_t leds[] = {LED_R_PIN, LED_G_PIN, LED_B_PIN, TP1_PIN, TP2_PIN};

  for (int i = 0; i < sizeof(leds); i++) {
    nrf_gpio_cfg_output(leds[i]);
    nrf_gpio_pin_set(leds[i]);
  }
}

static void gpio_init_button_pin(void) {
  nrfx_err_t status;
  nrfx_gpiote_in_config_t input_config =
      NRFX_GPIOTE_CONFIG_IN_SENSE_TOGGLE(true);

  nrfx_gpiote_init();
  status = nrfx_gpiote_in_init(BUTTON_PIN, &input_config, gpiote_event_handler);
  ERROR_CHECK("init", status);
  nrfx_gpiote_in_event_enable(BUTTON_PIN, true);
}

void gpio_init(void) {
  gpio_init_led_pins();
  gpio_init_button_pin();
}

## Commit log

2024-01-10 Project init
2024-01-10 add readme
2024-01-10 stream 24-01-10
2024-01-24 stream 24-01-24
2024-02-18 finishing touches in preparation for manufacturing
2024-02-18 add fabrication files
2024-02-25 finalize component values
2024-02-25 order components
2024-02-25 restructuring
2024-02-25 add notes
2024-02-25 add firmware
2024-02-25 add simulations
2024-02-25 stream 24-02-25
2024-03-05 generate BOM
2024-03-11 port to balancer hardware
2024-03-20 schematic error correction
2024-03-20 update notes
2024-03-20 firmware: implement multiplexer
2024-04-07 firmware: extensive architecture rework around adc sample swaps
2024-04-12 add Host-App for pillepalle73
2024-04-19 Host-App: added range switching
2024-05-07 firmware: history halfway through
2024-05-07 host app: hitory halfway through
2024-05-08 firmware: refactoring
2024-05-10 firmware + host app: 1h history functional
2024-05-19 firmware/host app: implement full history
2024-10-12 hardware: update to KiCad 7
2025-02-05 commit outstanding changes
2025-03-06 hardware: version 1
